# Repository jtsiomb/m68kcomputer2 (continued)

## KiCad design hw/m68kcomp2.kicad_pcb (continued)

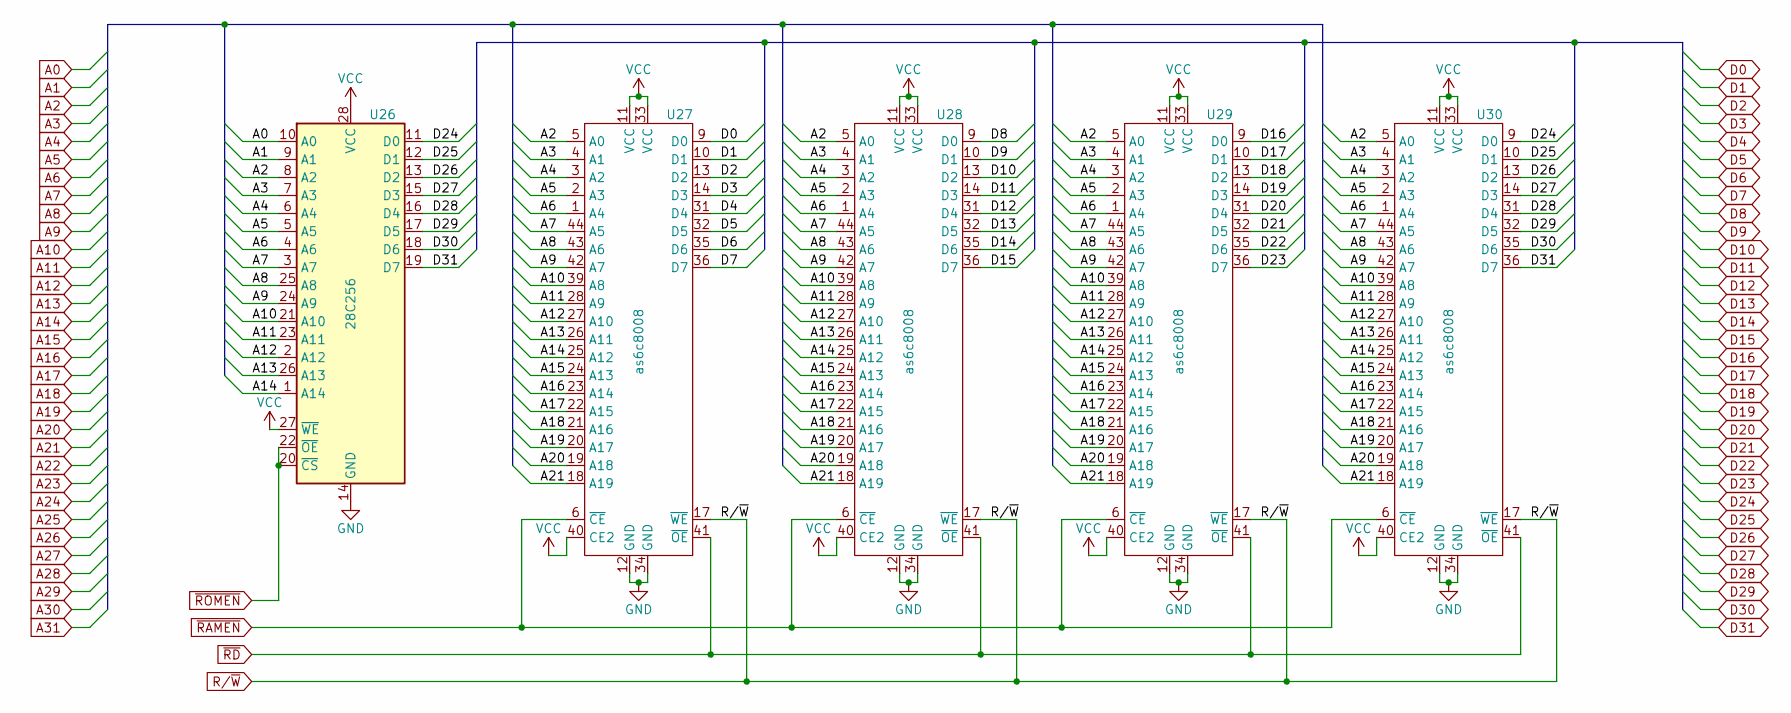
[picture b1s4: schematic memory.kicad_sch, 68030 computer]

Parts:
U26: 28C256; DIP-28_W15.24mm_Socket
U27, U28, U29, U30: as6c8008; TSOP-II-44_10.16x18.41mm_P0.8mm

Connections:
A0: U26.10 (A0); also elsewhere on the board
A1: U26.9 (A1); also elsewhere on the board
A2: U26.8 (A2), U27.5 (A0), U28.5 (A0), U29.5 (A0), U30.5 (A0); also elsewhere on the board
A3: U26.7 (A3), U27.4 (A1), U28.4 (A1), U29.4 (A1), U30.4 (A1); also elsewhere on the board
A4: U26.6 (A4), U27.3 (A2), U28.3 (A2), U29.3 (A2), U30.3 (A2); also elsewhere on the board
A5: U26.5 (A5), U27.2 (A3), U28.2 (A3), U29.2 (A3), U30.2 (A3); also elsewhere on the board
A6: U26.4 (A6), U27.1 (A4), U28.1 (A4), U29.1 (A4), U30.1 (A4); also elsewhere on the board
A7: U26.3 (A7), U27.44 (A5), U28.44 (A5), U29.44 (A5), U30.44 (A5); also elsewhere on the board
A8: U26.25 (A8), U27.43 (A6), U28.43 (A6), U29.43 (A6), U30.43 (A6); also elsewhere on the board
A9: U26.24 (A9), U27.42 (A7), U28.42 (A7), U29.42 (A7), U30.42 (A7); also elsewhere on the board
A10: U26.21 (A10), U27.39 (A8), U28.39 (A8), U29.39 (A8), U30.39 (A8); also elsewhere on the board
A11: U26.23 (A11), U27.28 (A9), U28.28 (A9), U29.28 (A9), U30.28 (A9); also elsewhere on the board
A12: U26.2 (A12), U27.27 (A10), U28.27 (A10), U29.27 (A10), U30.27 (A10); also elsewhere on the board
A13: U26.26 (A13), U27.26 (A11), U28.26 (A11), U29.26 (A11), U30.26 (A11); also elsewhere on the board
A14: U26.1 (A14), U27.25 (A12), U28.25 (A12), U29.25 (A12), U30.25 (A12); also elsewhere on the board
A15: U27.24 (A13), U28.24 (A13), U29.24 (A13), U30.24 (A13); also elsewhere on the board
A16: U27.23 (A14), U28.23 (A14), U29.23 (A14), U30.23 (A14); also elsewhere on the board
A17: U27.22 (A15), U28.22 (A15), U29.22 (A15), U30.22 (A15); also elsewhere on the board
A18: U27.21 (A16), U28.21 (A16), U29.21 (A16), U30.21 (A16); also elsewhere on the board
A19: U27.20 (A17), U28.20 (A17), U29.20 (A17), U30.20 (A17); also elsewhere on the board
A20: U27.19 (A18), U28.19 (A18), U29.19 (A18), U30.19 (A18); also elsewhere on the board
A21: U27.18 (A19), U28.18 (A19), U29.18 (A19), U30.18 (A19); also elsewhere on the board
D0: U27.9 (D0); also elsewhere on the board
D1: U27.10 (D1); also elsewhere on the board
D2: U27.13 (D2); also elsewhere on the board
D3: U27.14 (D3); also elsewhere on the board
D4: U27.31 (D4); also elsewhere on the board
D5: U27.32 (D5); also elsewhere on the board
D6: U27.35 (D6); also elsewhere on the board
D7: U27.36 (D7); also elsewhere on the board
D8: U28.9 (D0); also elsewhere on the board
D9: U28.10 (D1); also elsewhere on the board
D10: U28.13 (D2); also elsewhere on the board
D11: U28.14 (D3); also elsewhere on the board
D12: U28.31 (D4); also elsewhere on the board
D13: U28.32 (D5); also elsewhere on the board
D14: U28.35 (D6); also elsewhere on the board
D15: U28.36 (D7); also elsewhere on the board
D16: U29.9 (D0); also elsewhere on the board
D17: U29.10 (D1); also elsewhere on the board
D18: U29.13 (D2); also elsewhere on the board
D19: U29.14 (D3); also elsewhere on the board
D20: U29.31 (D4); also elsewhere on the board
D21: U29.32 (D5); also elsewhere on the board
D22: U29.35 (D6); also elsewhere on the board
D23: U29.36 (D7); also elsewhere on the board
D24: U26.11 (D0), U30.9 (D0); also elsewhere on the board
D25: U26.12 (D1), U30.10 (D1); also elsewhere on the board
D26: U26.13 (D2), U30.13 (D2); also elsewhere on the board
D27: U26.15 (D3), U30.14 (D3); also elsewhere on the board
D28: U26.16 (D4), U30.31 (D4); also elsewhere on the board
D29: U26.17 (D5), U30.32 (D5); also elsewhere on the board
D30: U26.18 (D6), U30.35 (D6); also elsewhere on the board
D31: U26.19 (D7), U30.36 (D7); also elsewhere on the board
GND: U26.14 (GND), U27.12 (GND), U27.34 (GND), U28.12 (GND), U28.34 (GND), U29.12 (GND), U29.34 (GND), U30.12 (GND), U30.34 (GND); also elsewhere on the board
R/~W: U27.17 (~WE), U28.17 (~WE), U29.17 (~WE), U30.17 (~WE); also elsewhere on the board
VCC: U26.27 (~WE), U26.28 (VCC), U27.11 (VCC), U27.33 (VCC), U27.40 (CE2), U28.11 (VCC), U28.33 (VCC), U28.40 (CE2), U29.11 (VCC), U29.33 (VCC), U29.40 (CE2), U30.11 (VCC), U30.33 (VCC), U30.40 (CE2); also elsewhere on the board
~RAMEN: U27.6 (~CE), U28.6 (~CE), U29.6 (~CE), U30.6 (~CE)
~RD: U27.41 (~OE), U28.41 (~OE), U29.41 (~OE), U30.41 (~OE); also elsewhere on the board
~ROMEN: U26.20 (~CS), U26.22 (~OE)

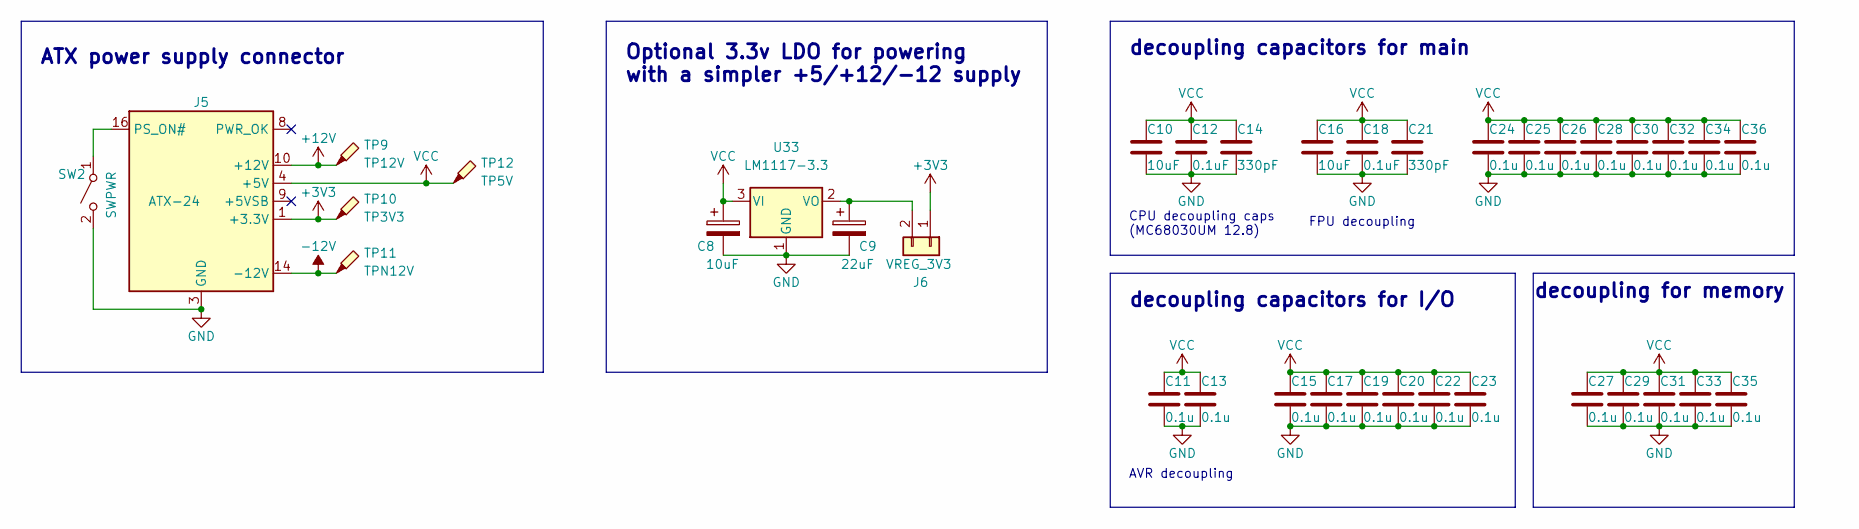
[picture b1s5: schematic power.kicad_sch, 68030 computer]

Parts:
C8: 10uF; CP_Elec_4x4.5
C9: 22uF; CP_Elec_4x4.5
C10, C16: 10uF; C_0805_2012Metric_Pad1.18x1.45mm_HandSolder
C11, C13, C15, C17, C19, C20, C22, C23, C24, C25, C26, C27, C28, C29, C30, C31, C32, C33, C34, C35, C36: 0.1u; C_0805_2012Metric_Pad1.18x1.45mm_HandSolder
C12, C18: 0.1uF; C_0805_2012Metric_Pad1.18x1.45mm_HandSolder
C14, C21: 330pF; C_0805_2012Metric_Pad1.18x1.45mm_HandSolder
J5: ATX-24; Molex_Mini-Fit_Jr_5566-24A_2x12_P4.20mm_Vertical
J6: VREG_3V3; PinHeader_1x02_P2.54mm_Vertical
SW2: SWPWR; PinHeader_1x02_P2.54mm_Vertical
TP9: TP12V; TestPoint_Pad_D1.5mm
TP10: TP3V3; TestPoint_Pad_D1.5mm
TP11: TPN12V; TestPoint_Pad_D1.5mm
TP12: TP5V; TestPoint_Pad_D1.5mm
U33: LM1117-3.3; SOT-223-3_TabPin2

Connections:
+3V3: J5.1 (+3.3V), J5.2 (+3.3V), J5.12 (+3.3V), J5.13 (+3.3V), J6.1, TP10.1; also elsewhere on the board
+12V: J5.10 (+12V), J5.11 (+12V), TP9.1; also elsewhere on the board
-12V: J5.14 (-12V), TP11.1; also elsewhere on the board
GND: C8.2, C9.2, C10.2, C11.2, C12.2, C13.2, C14.2, C15.2, C16.2, C17.2, C18.2, C19.2, C20.2, C21.2, C22.2, C23.2, C24.2, C25.2, C26.2, C27.2, C28.2, C29.2, C30.2, C31.2, C32.2, C33.2, C34.2, C35.2, C36.2, J5.3 (GND), J5.5 (GND), J5.7 (GND), J5.15 (GND), J5.17 (GND), J5.18 (GND), J5.19 (GND), J5.24 (GND), SW2.2 (B), U33.1 (GND); also elsewhere on the board
unnamed: C9.1, J6.2, U33.2 (VO)
unnamed: J5.16 (PS_ON#), SW2.1 (A)
VCC: C8.1, C10.1, C11.1, C12.1, C13.1, C14.1, C15.1, C16.1, C17.1, C18.1, C19.1, C20.1, C21.1, C22.1, C23.1, C24.1, C25.1, C26.1, C27.1, C28.1, C29.1, C30.1, C31.1, C32.1, C33.1, C34.1, C35.1, C36.1, J5.4 (+5V), J5.6 (+5V), J5.21 (+5V), J5.22 (+5V), J5.23 (+5V), TP12.1, U33.3 (VI); also elsewhere on the board

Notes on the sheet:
ATX power supply connector
decoupling capacitors for main
decoupling capacitors for I/O
AVR decoupling
CPU decoupling caps (MC68030UM 12.8)
decoupling for memory
Optional 3.3v LDO for powering with a simpler +5/+12/-12 supply
FPU decoupling

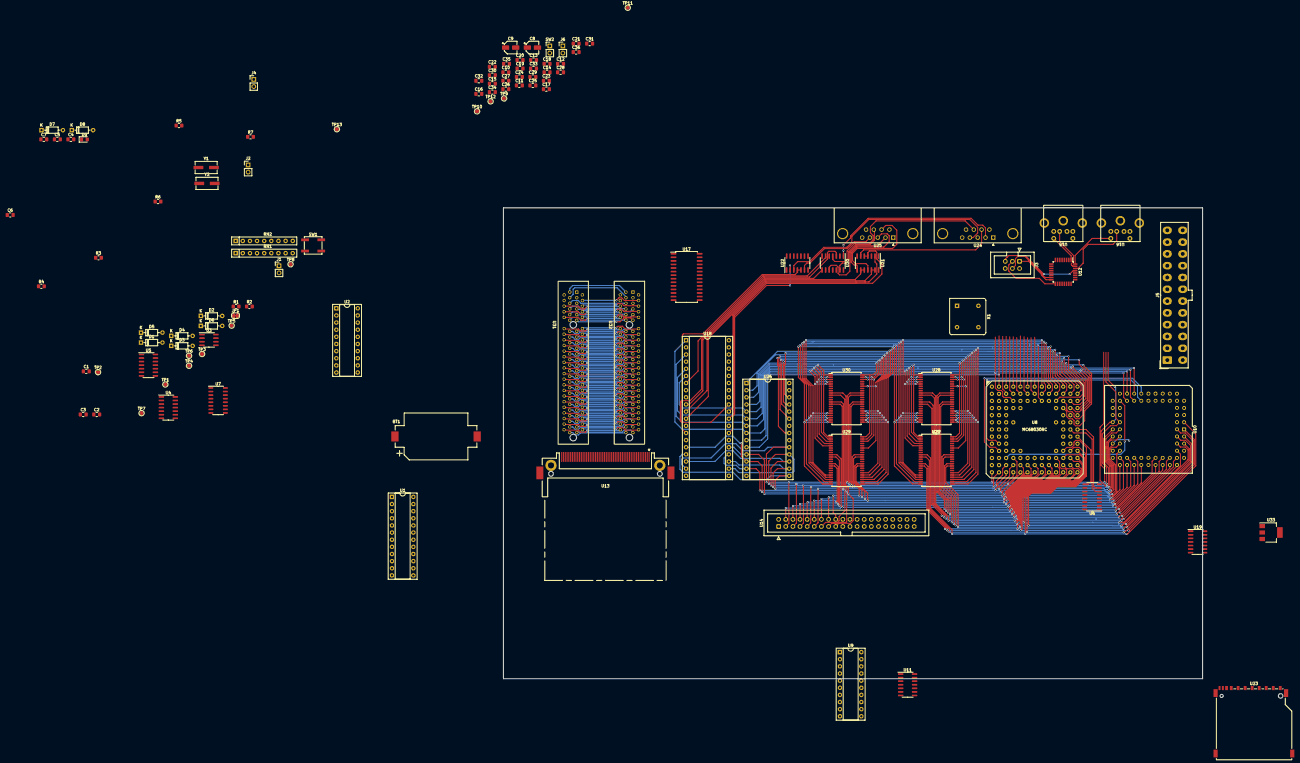
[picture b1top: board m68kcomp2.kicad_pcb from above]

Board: 4 copper layers, 248.9 x 167.6 mm, 113 parts (0 on the bottom side), 176 nets.

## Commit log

2019-02-05 finished the 68881 symbol, and added a few major components on a schematic sheet
2019-02-05 updated the readme and added license files
2022-01-29 68030 symbol and footprint
2022-01-29 added SRAM symbol
2022-01-31 Symbols and rough schematic islands:
    - mc68881 fpu
    - mc68681 duart
    - static ram
    - interrupt priority and acknowledge
2022-01-31 address decoding
2022-02-01 BERR watchdog
2022-02-01 simplified ram/rom dsack, reset watchdog on system reset, cache inhibit on I/O
2022-02-04 progress
2022-02-04 schematic progress
2022-02-07 avr handling SD card, keyboard, and mouse ports
2022-02-08 schematic progress, split iodecode from glue.pld...
2022-02-09 ATA connector
2022-02-09 broken up into multiple sheets, and added IOWAIT input to the watchdog
2022-02-09 expansion, compactflash connector, 3v3reg jumper
2022-02-09 separate power sheet
2022-02-10 decoupling, test points, and ATA0EN/ATA1EN in iodecode.pld
2022-02-10 updated readme and license
2022-02-10 fixed ERC errors
2022-02-10 first pass at assigning footprints
2022-02-22 added expansion slot footprint (PCI-e 8x)
2022-02-24 finished the footprints
2022-02-24 added shield pin in ps2conn symbol, fixed ERC
2022-02-25 fixed swapped pin-name/number fields in rs232 connector symbol
2022-02-25 fixed resistor footprint assignments, changed PCB to 4-layer
2022-02-26 started laying out board
2022-02-27 pcb layout progress
2022-03-01 32bit buses take a lot of space
2022-03-09 more pcb layout
2022-03-10 cleaned up some of the bus traces
